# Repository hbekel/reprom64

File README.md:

#reprom64
*rom replacement board for the C64*

This is a rom adapter board for the C64 which replaces all rom chips
with a single 64kb 27C512 Eprom, offering space for four different
kernals, four charsets and two basic roms.

It can be assembled for any C64 mainboard as well as for the SX64 CPU
board.

Please refer to the [project
page](http://www.henning-bekel.de/reprom64) for detailed
documentation.

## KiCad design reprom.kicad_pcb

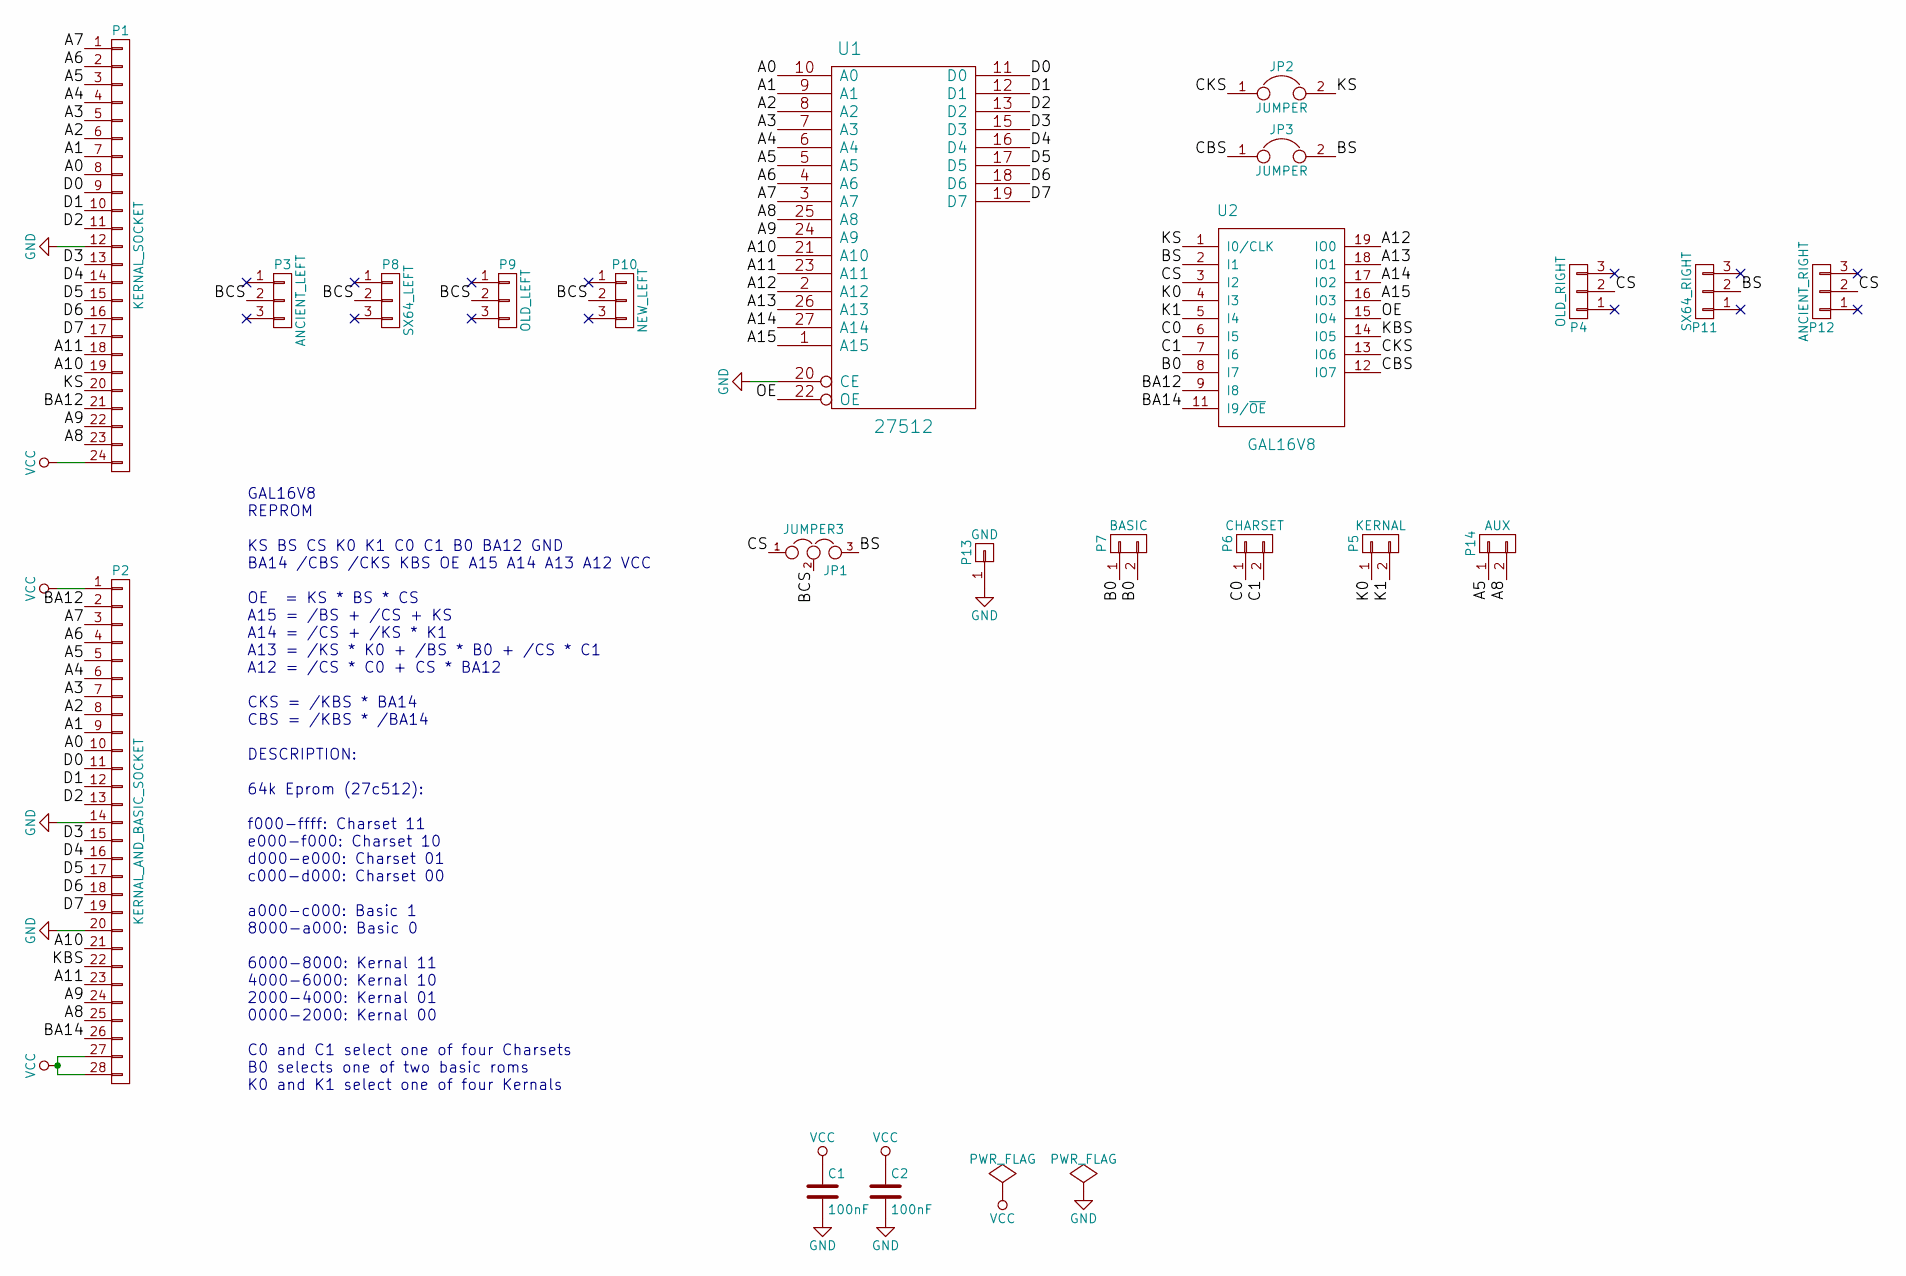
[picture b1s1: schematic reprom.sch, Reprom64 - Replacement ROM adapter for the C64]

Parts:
C1, C2: 100nF; C_Disc_D3_P2.5
JP1: JUMPER3; Pin_Header_Straight_1x03
JP2, JP3: JUMPER; Pin_Header_Straight_1x02
P1: KERNAL_SOCKET; DIP-24_W15.24mm
P2: KERNAL_AND_BASIC_SOCKET; DIP-28_W15.24mm
P3: ANCIENT_LEFT; Pin_Header_Straight_1x03
P4: OLD_RIGHT; Pin_Header_Straight_1x03
P5: KERNAL; Pin_Header_Straight_1x02
P6: CHARSET; Pin_Header_Straight_1x02
P7: BASIC; Pin_Header_Straight_1x02
P8: SX64_LEFT; Pin_Header_Straight_1x03
P9: OLD_LEFT; Pin_Header_Straight_1x03
P10: NEW_LEFT; Pin_Header_Straight_1x03
P11: SX64_RIGHT; Pin_Header_Straight_1x03
P12: ANCIENT_RIGHT; Pin_Header_Straight_1x03
P13: GND; Pin_Header_Straight_1x01
P14: AUX; Pin_Header_Straight_1x02
U1: 27512; DIP-28_W15.24mm
U2: GAL16V8; DIP-20_W7.62mm

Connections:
/A0: P1.8, P2.10, U1.10 (A0)
/A1: P1.7, P2.9, U1.9 (A1)
/A2: P1.6, P2.8, U1.8 (A2)
/A3: P1.5, P2.7, U1.7 (A3)
/A4: P1.4, P2.6, U1.6 (A4)
/A5: P1.3, P2.5, P14.1, U1.5 (A5)
/A6: P1.2, P2.4, U1.4 (A6)
/A7: P1.1, P2.3, U1.3 (A7)
/A8: P1.23, P2.25, P14.2, U1.25 (A8)
/A9: P1.22, P2.24, U1.24 (A9)
/A10: P1.19, P2.21, U1.21 (A10)
/A11: P1.18, P2.23, U1.23 (A11)
/A12: U1.2 (A12), U2.19 (IO0)
/A13: U1.26 (A13), U2.18 (IO1)
/A14: U1.27 (A14), U2.17 (IO2)
/A15: U1.1 (A15), U2.16 (IO3)
/B0: P7.1, P7.2, U2.8 (I7)
/BA12: P1.21, P2.2, U2.9 (I8)
/BA14: P2.26, U2.11 (I9/~OE)
/BCS: JP1.2, P3.2, P8.2, P9.2, P10.2
/BS: JP1.3, JP3.2, P11.2, U2.2 (I1)
/C0: P6.1, U2.6 (I5)
/C1: P6.2, U2.7 (I6)
/CBS: JP3.1, U2.12 (IO7)
/CKS: JP2.1, U2.13 (IO6)
/CS: JP1.1, P4.2, P12.2, U2.3 (I2)
/D0: P1.9, P2.11, U1.11 (D0)
/D1: P1.10, P2.12, U1.12 (D1)
/D2: P1.11, P2.13, U1.13 (D2)
/D3: P1.13, P2.15, U1.15 (D3)
/D4: P1.14, P2.16, U1.16 (D4)
/D5: P1.15, P2.17, U1.17 (D5)
/D6: P1.16, P2.18, U1.18 (D6)
/D7: P1.17, P2.19, U1.19 (D7)
/K0: P5.1, U2.4 (I3)
/K1: P5.2, U2.5 (I4)
/KBS: P2.22, U2.14 (IO5)
/KS: JP2.2, P1.20, U2.1 (I0/CLK)
/OE: U1.22 (OE), U2.15 (IO4)
GND: C1.2, C2.2, P1.12, P2.14, P2.20, P13.1, U1.14 (GND), U1.20 (CE), U2.10 (GND)
VCC: C1.1, C2.1, P1.24, P2.1, P2.27, P2.28, U1.28 (VCC), U2.20 (VCC)

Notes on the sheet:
GAL16V8 REPROM KS BS CS K0 K1 C0 C1 B0 BA12 GND BA14 /CBS /CKS KBS OE A15 A14 A13 A12 VCC OE = KS * BS * CS A15 = /BS + /CS + KS A14 = /CS + /KS * K1 A13 = /KS * K0 + /BS * B0 + /CS * C1 A12 = /CS * C0 + CS * BA12 CKS = /KBS * BA14 CBS = /KBS * /BA14 DESCRIPTION: 64k Eprom (27c512): f000-ffff: Char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

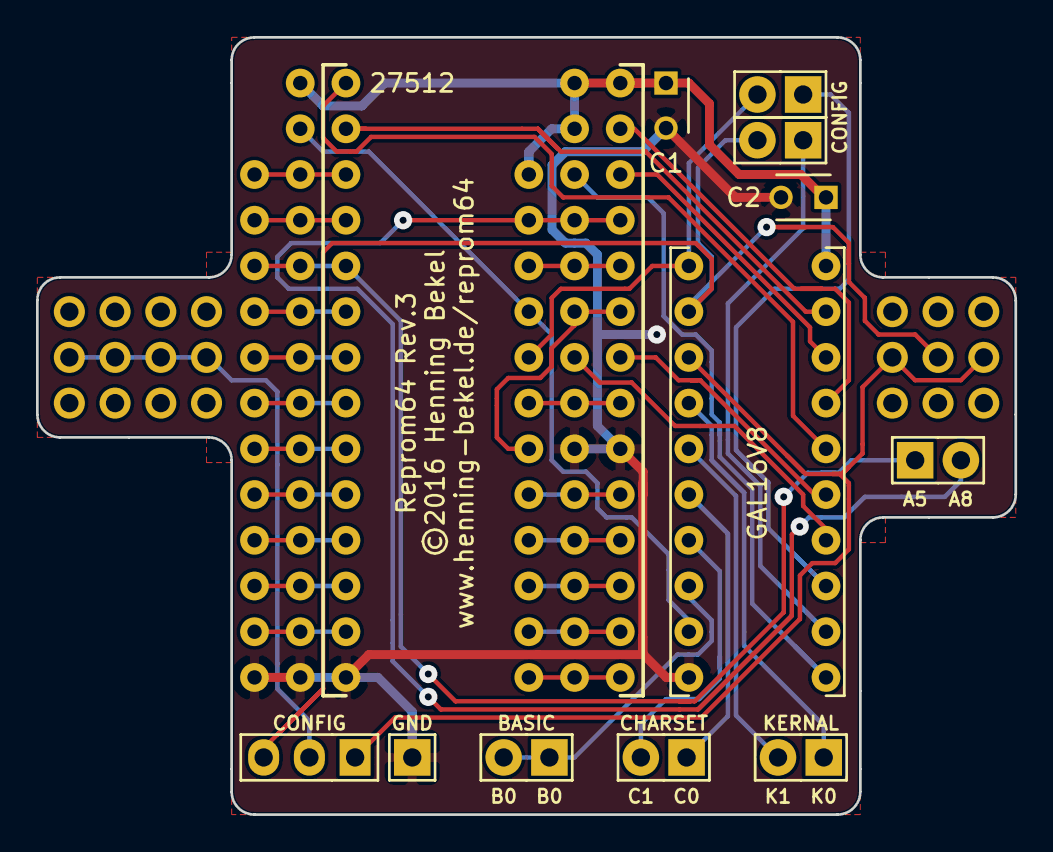
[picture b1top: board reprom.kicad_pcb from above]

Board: 2 copper layers, 54.4 x 43.2 mm, 21 parts (0 on the bottom side), 41 nets.

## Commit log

2016-01-18 Firmware: Fixed computed kernal and basic select signals (invert outputs)
2016-01-18 Hardware: Removed crappy autorouting, improved part placement
2016-01-18 Added readme and license files
2016-01-18 Hardware: Some initial routing
2016-01-19 Hardware: Improved routing, designed silkscreen, improved schematics
2016-01-19 Hardware: Improved routing
2016-01-20 Hardware: Revision 1 (prototype), added gerber files
2016-03-07 Housekeeping: changed file modes for non-executable files
2016-03-08 Version 1.0
2016-03-08 Makefile: added release target
2016-03-10 Added Makefile and default roms for creating suitable eprom images
2016-03-16 Hardware: Added additional pin headers for wider rom layouts (KU/326298)
2016-03-16 Revert "Hardware: Added additional pin headers for wider rom layouts (KU/326298)"
    This reverts commit 2e8d7ef8814329ef0b47112793623fe7f19c62f6.
2016-03-17 Hardware: Added support for all board types
    This adds the pin headers required to use the adapter
    on ancient boards (396298 and KU14194HB) and on the
    SX64 CPU board (251102).
2016-03-22 Hardware: Improved silkscreen, added board rev info
2016-03-22 Documentation: Added gimp image showing different assembly options
2016-03-29 Documentation: Added renderings of different assembly options
2016-03-29 Housekeeping: Removed gerber files, fixed file modes, Version bumped
    Since different board houses have different requirements for gerber files,
    it makes no sense to put them into the repository.
2016-03-29 Version 1.1
2016-05-29 Hardware: Added GND connector, improved layout, silkscreen and 3d view
2016-05-30 Hardware: Added Revision 2 gerber files for production
2016-05-30 Hardware: Removed gerber files for development
2016-05-31 Hardware: Fixed header placement, added Revision 2 gerber files again
    Fixed pin header placement (now on 2.54mm grid to allow single connector).
2016-06-01 Version 1.2
    Only minor changes in this version:
    * Added pin header for GND
    * Aligned pin headers in 2.54mm Spacing (0.1")
2016-06-01 Makefile: Fixed firmware filename in release target
2016-07-28 Hardware: Added additional pin header for A5 and A8, rounded corners
2016-08-17 Hardware: Moved A5 and A8 header to a more convenient location
2016-08-18 Hardware: Improved silkscreen, routing
2016-08-22 Hardware: Reversed order of A5 and A8
2016-08-22 Version 1.3 Revision 3, added gerber files
2020-09-15 Fixed wrong order of ROMs in image/Makefile
    Reported by djtulan
2021-12-17 Makefile: Added program target for programming ATF16V8B via minipro

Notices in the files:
reprom.kicad_pcb:
©2016 Henning Bekel
